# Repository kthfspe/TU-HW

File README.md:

# HW.template
Template for KiCAD PCB projects

## How to name your project
The kicad project name should be the name of the repo without the "-HW" part. For example EBS-HW repo should contain EBS.pro KiCAD project.  

The KiCAD project should be in the top level folder of the repo, i.e. no additional folders containing the KiCAD project should be there. To achieve that you will need to unselect an option when creating the project

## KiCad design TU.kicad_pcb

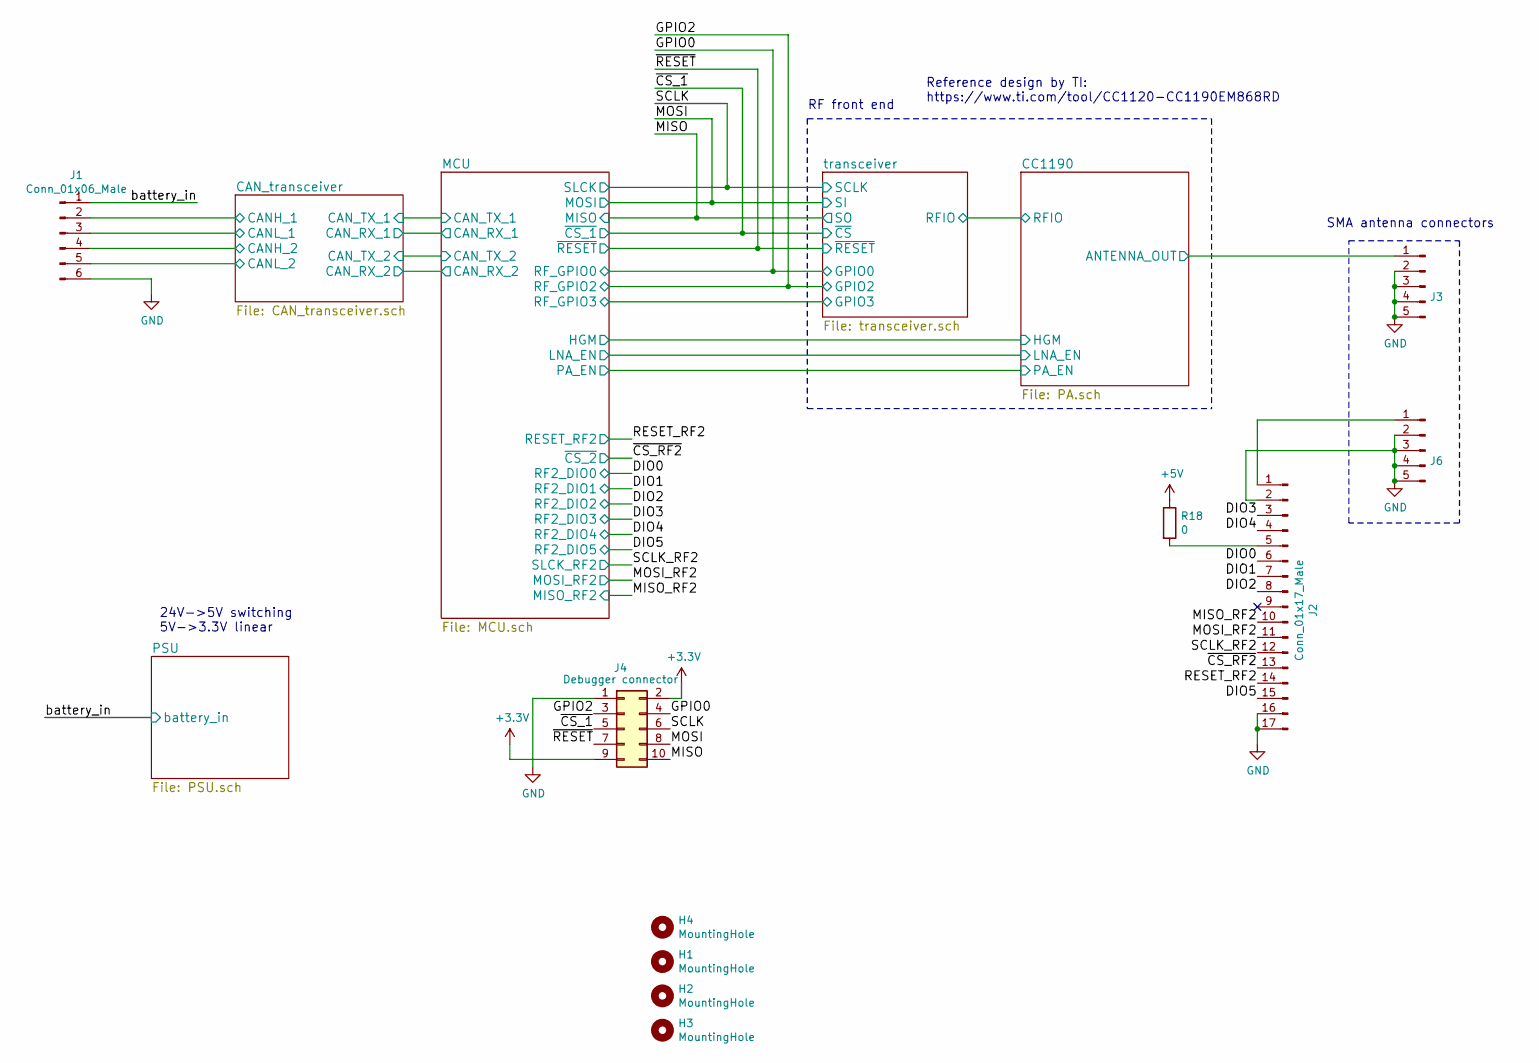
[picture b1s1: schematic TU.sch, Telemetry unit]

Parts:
H1, H2, H3, H4: MountingHole; MountingHole_2.5mm
J1: Conn_01x06_Male; TE_282834-6
J2: Conn_01x17_Male; RFM95PW
J3, J6: Conn_01x05_Male; Wurth_SMA_60312002114503
J4: Debugger connector; PinHeader_2x05_P2.54mm_Vertical
R18: 0; R_0603_1608Metric

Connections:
+3V3: J4.2, J4.9; also elsewhere on the board
+5V: R18.1; also elsewhere on the board
/CAN_transceiver/CANH_1: J1.2; also elsewhere on the board
/CAN_transceiver/CANH_2: J1.4; also elsewhere on the board
/CAN_transceiver/CANL_1: J1.3; also elsewhere on the board
/CAN_transceiver/CANL_2: J1.5; also elsewhere on the board
/CC1190/ANTENNA_OUT: J3.1; also elsewhere on the board
/DIO0: J2.6; also elsewhere on the board
/DIO1: J2.7; also elsewhere on the board
/DIO2: J2.8; also elsewhere on the board
/DIO3: J2.3; also elsewhere on the board
/DIO4: J2.4; also elsewhere on the board
/DIO5: J2.15; also elsewhere on the board
/GPIO0: J4.4; also elsewhere on the board
/GPIO2: J4.3; also elsewhere on the board
/MISO: J4.10; also elsewhere on the board
/MISO_RF2: J2.10; also elsewhere on the board
/MOSI: J4.8; also elsewhere on the board
/MOSI_RF2: J2.11; also elsewhere on the board
/RESET_RF2: J2.14; also elsewhere on the board
/SCLK: J4.6; also elsewhere on the board
/SCLK_RF2: J2.12; also elsewhere on the board
/battery_in: J1.1; also elsewhere on the board
/~CS_1: J4.5; also elsewhere on the board
/~CS_RF2: J2.13; also elsewhere on the board
/~RESET: J4.7; also elsewhere on the board
GND: J1.6, J2.2, J2.16, J2.17, J3.2, J3.3, J3.4, J3.5, J4.1, J6.2, J6.3, J6.4, J6.5; also elsewhere on the board
unnamed: J2.1, J6.1
unnamed: J2.5, R18.2

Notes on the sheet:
24V->5V switching 5V->3.3V linear
RF front end
SMA antenna connectors
Reference design by TI: https://www.ti.com/tool/CC1120-CC1190EM868RD

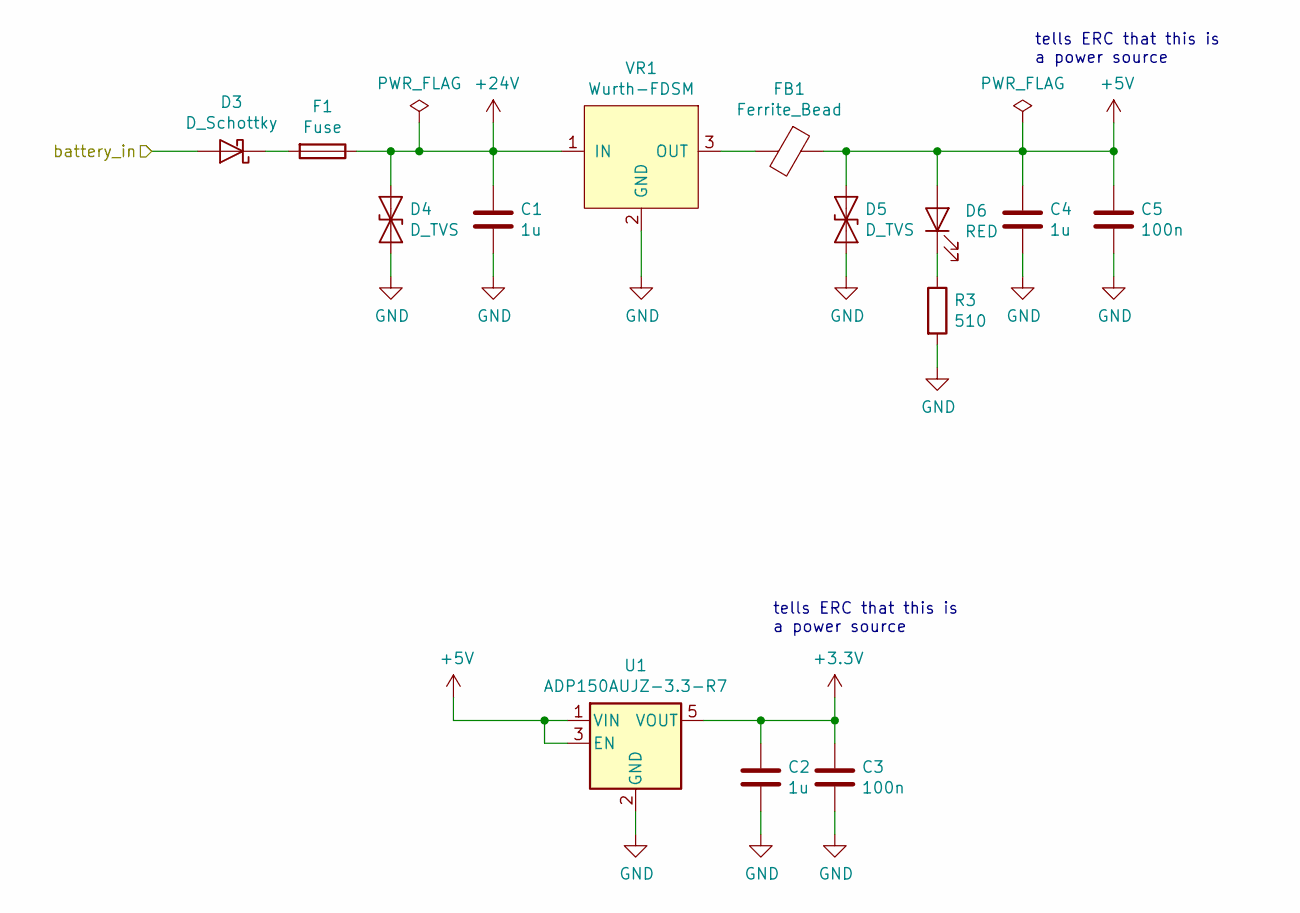
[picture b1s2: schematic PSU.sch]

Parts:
C1, C2: 1u; C_0805_2012Metric
C3, C5: 100n; C_0603_1608Metric
C4: 1u; C_0603_1608Metric
D3: D_Schottky; D_SOD-323
D4, D5: D_TVS; D_SOD-323
D6: RED; D_SOD-323
F1: Fuse; Fuse_0805_2012Metric
FB1: Ferrite_Bead; C_0805_2012Metric
R3: 510; R_0603_1608Metric
U1: ADP150AUJZ-3.3-R7; SOT-23-5
VR1: Wurth-FDSM

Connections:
+3V3: C2.1, C3.1, U1.5 (VOUT); also elsewhere on the board
+5V: C4.1, C5.1, D5.1 (A1), D6.2 (A), FB1.1, U1.1 (VIN), U1.3 (EN); also elsewhere on the board
+24V: C1.1, D4.1 (A1), F1.1, VR1.1 (IN)
/battery_in: D3.2 (A); also elsewhere on the board
GND: C1.2, C2.2, C3.2, C4.2, C5.2, D4.2 (A2), D5.2 (A2), R3.2, U1.2 (GND), VR1.2 (GND); also elsewhere on the board
unnamed: D3.1 (K), F1.2
unnamed: D6.1 (K), R3.1
unnamed: FB1.2, VR1.3 (OUT)

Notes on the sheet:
tells ERC that this is a power source

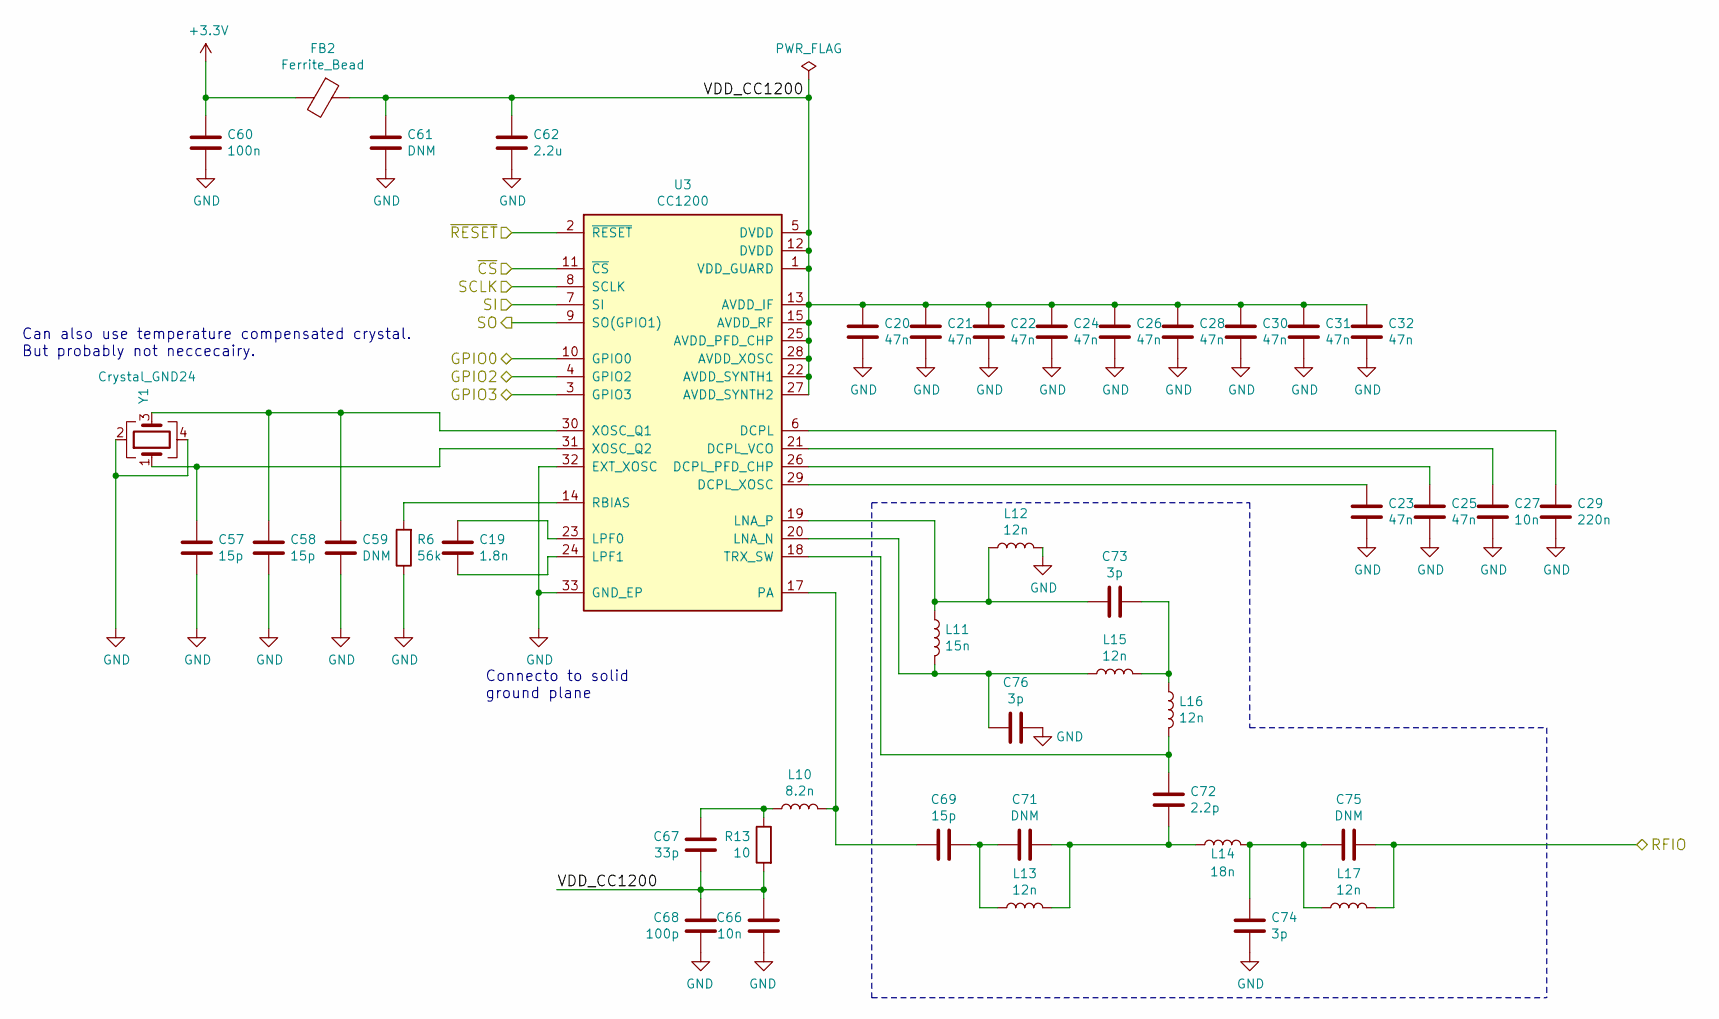
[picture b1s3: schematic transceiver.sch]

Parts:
C19: 1.8n; C_0603_1608Metric
C20, C21, C22, C23, C24, C25, C26, C28, C30, C31, C32: 47n; C_0603_1608Metric
C27, C66: 10n; C_0603_1608Metric
C29: 220n; C_0603_1608Metric
C57, C58, C69: 15p; C_0603_1608Metric
C59, C61, C71, C75: DNM; C_0603_1608Metric
C60: 100n; C_0603_1608Metric
C62: 2.2u; C_0603_1608Metric
C67: 33p; C_0603_1608Metric
C68: 100p; C_0603_1608Metric
C72: 2.2p; C_0603_1608Metric
C73, C74, C76: 3p; C_0603_1608Metric
FB2: Ferrite_Bead; C_0805_2012Metric
L10: 8.2n; L_0603_1608Metric
L11: 15n; L_0603_1608Metric
L12, L13, L15, L16, L17: 12n; L_0603_1608Metric
L14: 18n; L_0603_1608Metric
R6: 56k; R_0603_1608Metric
R13: 10; R_0603_1608Metric
U3: CC1200; QFN-32-1EP_5x5mm_P0.5mm_EP3.45x3.45mm
Y1: Crystal_GND24; ndk_08142018_NX3225SA

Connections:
+3V3: C60.1, FB2.2; also elsewhere on the board
/CC1190/RFIO: C75.1, L17.2; also elsewhere on the board
/GPIO0: U3.10 (GPIO0); also elsewhere on the board
/GPIO2: U3.4 (GPIO2); also elsewhere on the board
/MISO: U3.9 (SO(GPIO1)); also elsewhere on the board
/MOSI: U3.7 (SI); also elsewhere on the board
/SCLK: U3.8 (SCLK); also elsewhere on the board
/transceiver/GPIO3: U3.3 (GPIO3); also elsewhere on the board
/transceiver/VDD_CC1200: C20.1, C21.1, C22.1, C24.1, C26.1, C28.1, C30.1, C31.1, C32.1, C61.1, C62.1, C66.1, C67.2, C68.1, FB2.1, R13.2, U3.1 (VDD_GUARD), U3.5 (DVDD), U3.12 (DVDD), U3.13 (AVDD_IF), U3.15 (AVDD_RF), U3.22 (AVDD_SYNTH1), U3.25 (AVDD_PFD_CHP), U3.27 (AVDD_SYNTH2), U3.28 (AVDD_XOSC)
/~CS_1: U3.11 (~CS~); also elsewhere on the board
/~RESET: U3.2 (~RESET~); also elsewhere on the board
GND: C20.2, C21.2, C22.2, C23.2, C24.2, C25.2, C26.2, C27.2, C28.2, C29.2, C30.2, C31.2, C32.2, C57.2, C58.2, C59.2, C60.2, C61.2, C62.2, C66.2, C68.2, C74.2, C76.1, L12.2, R6.1, U3.32 (EXT_XOSC), U3.33 (GND_EP), Y1.2, Y1.4; also elsewhere on the board
unnamed: C19.1, U3.23 (LPF0)
unnamed: C19.2, U3.24 (LPF1)
unnamed: C23.1, U3.29 (DCPL_XOSC)
unnamed: C25.1, U3.26 (DCPL_PFD_CHP)
unnamed: C27.1, U3.21 (DCPL_VCO)
unnamed: C29.1, U3.6 (DCPL)
unnamed: C57.1, U3.31 (XOSC_Q2), Y1.1
unnamed: C58.1, C59.1, U3.30 (XOSC_Q1), Y1.3
unnamed: C67.1, L10.1, R13.1
unnamed: C69.1, C71.2, L13.1
unnamed: C69.2, L10.2, U3.17 (PA)
unnamed: C71.1, C72.2, L13.2, L14.1
unnamed: C72.1, L16.2, U3.18 (TRX_SW)
unnamed: C73.1, L15.2, L16.1
unnamed: C73.2, L11.1, L12.1, U3.19 (LNA_P)
unnamed: C74.1, C75.2, L14.2, L17.1
unnamed: C76.2, L11.2, L15.1, U3.20 (LNA_N)
unnamed: R6.2, U3.14 (RBIAS)

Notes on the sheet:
Connecto to solid ground plane
Can also use temperature compensated crystal. But probably not neccecairy.

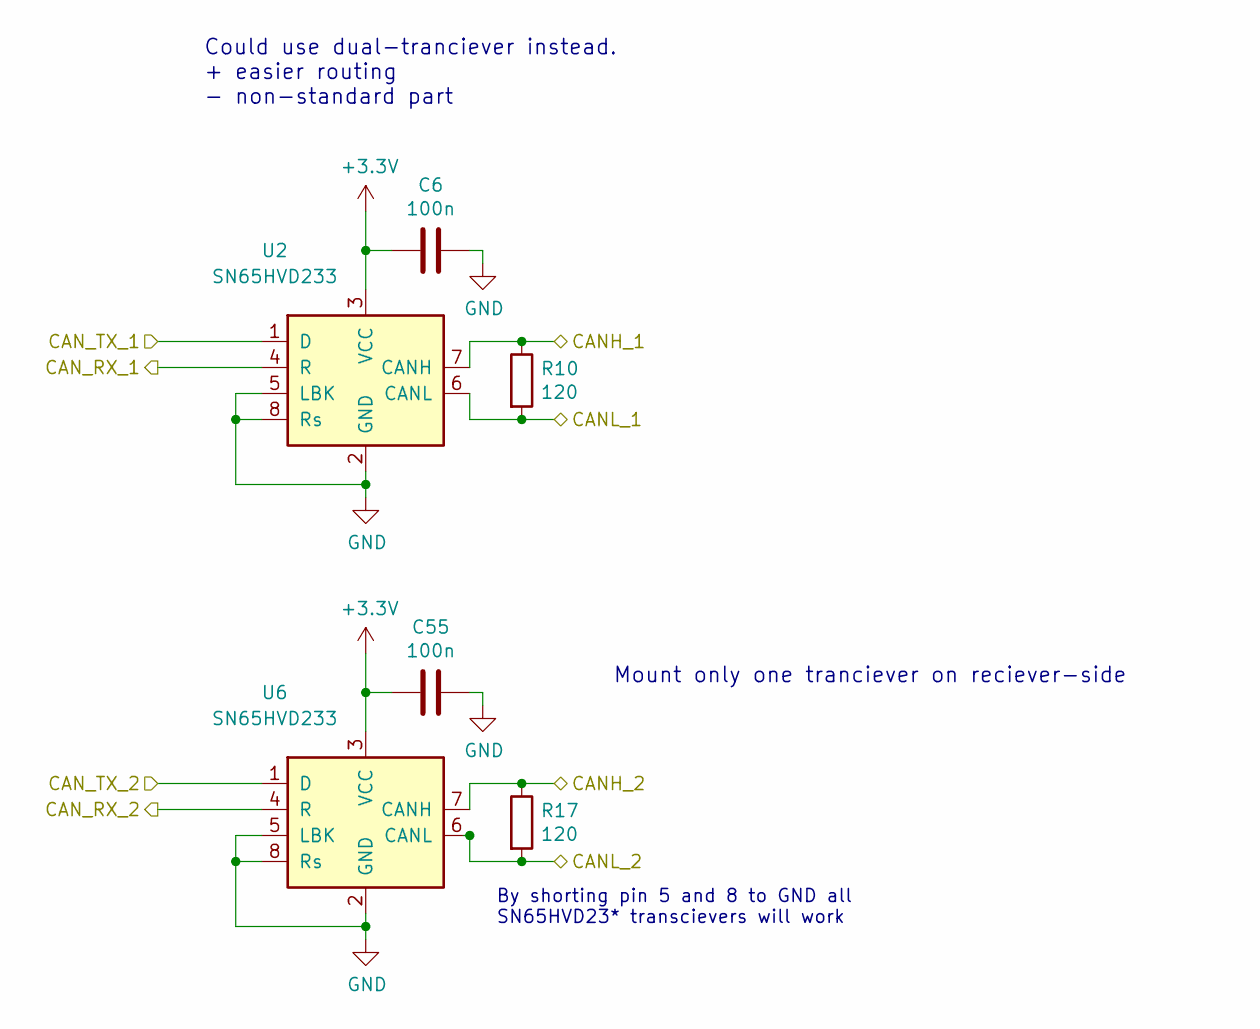
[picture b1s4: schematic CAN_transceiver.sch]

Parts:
C6, C55: 100n; C_0603_1608Metric
R10, R17: 120; R_0603_1608Metric
U2, U6: SN65HVD233; SOIC-8_3.9x4.9mm_P1.27mm

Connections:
+3V3: C6.2, C55.2, U2.3 (VCC), U6.3 (VCC); also elsewhere on the board
/CAN_transceiver/CANH_1: R10.1, U2.7 (CANH); also elsewhere on the board
/CAN_transceiver/CANH_2: R17.1, U6.7 (CANH); also elsewhere on the board
/CAN_transceiver/CANL_1: R10.2, U2.6 (CANL); also elsewhere on the board
/CAN_transceiver/CANL_2: R17.2, U6.6 (CANL); also elsewhere on the board
/CAN_transceiver/CAN_RX_1: U2.4 (R); also elsewhere on the board
/CAN_transceiver/CAN_RX_2: U6.4 (R); also elsewhere on the board
/CAN_transceiver/CAN_TX_1: U2.1 (D); also elsewhere on the board
/CAN_transceiver/CAN_TX_2: U6.1 (D); also elsewhere on the board
GND: C6.1, C55.1, U2.2 (GND), U2.5 (LBK), U2.8 (Rs), U6.2 (GND), U6.5 (LBK), U6.8 (Rs); also elsewhere on the board

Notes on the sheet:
By shorting pin 5 and 8 to GND all SN65HVD23* transcievers will work
Could use dual-tranciever instead. + easier routing - non-standard part
Mount only one tranciever on reciever-side

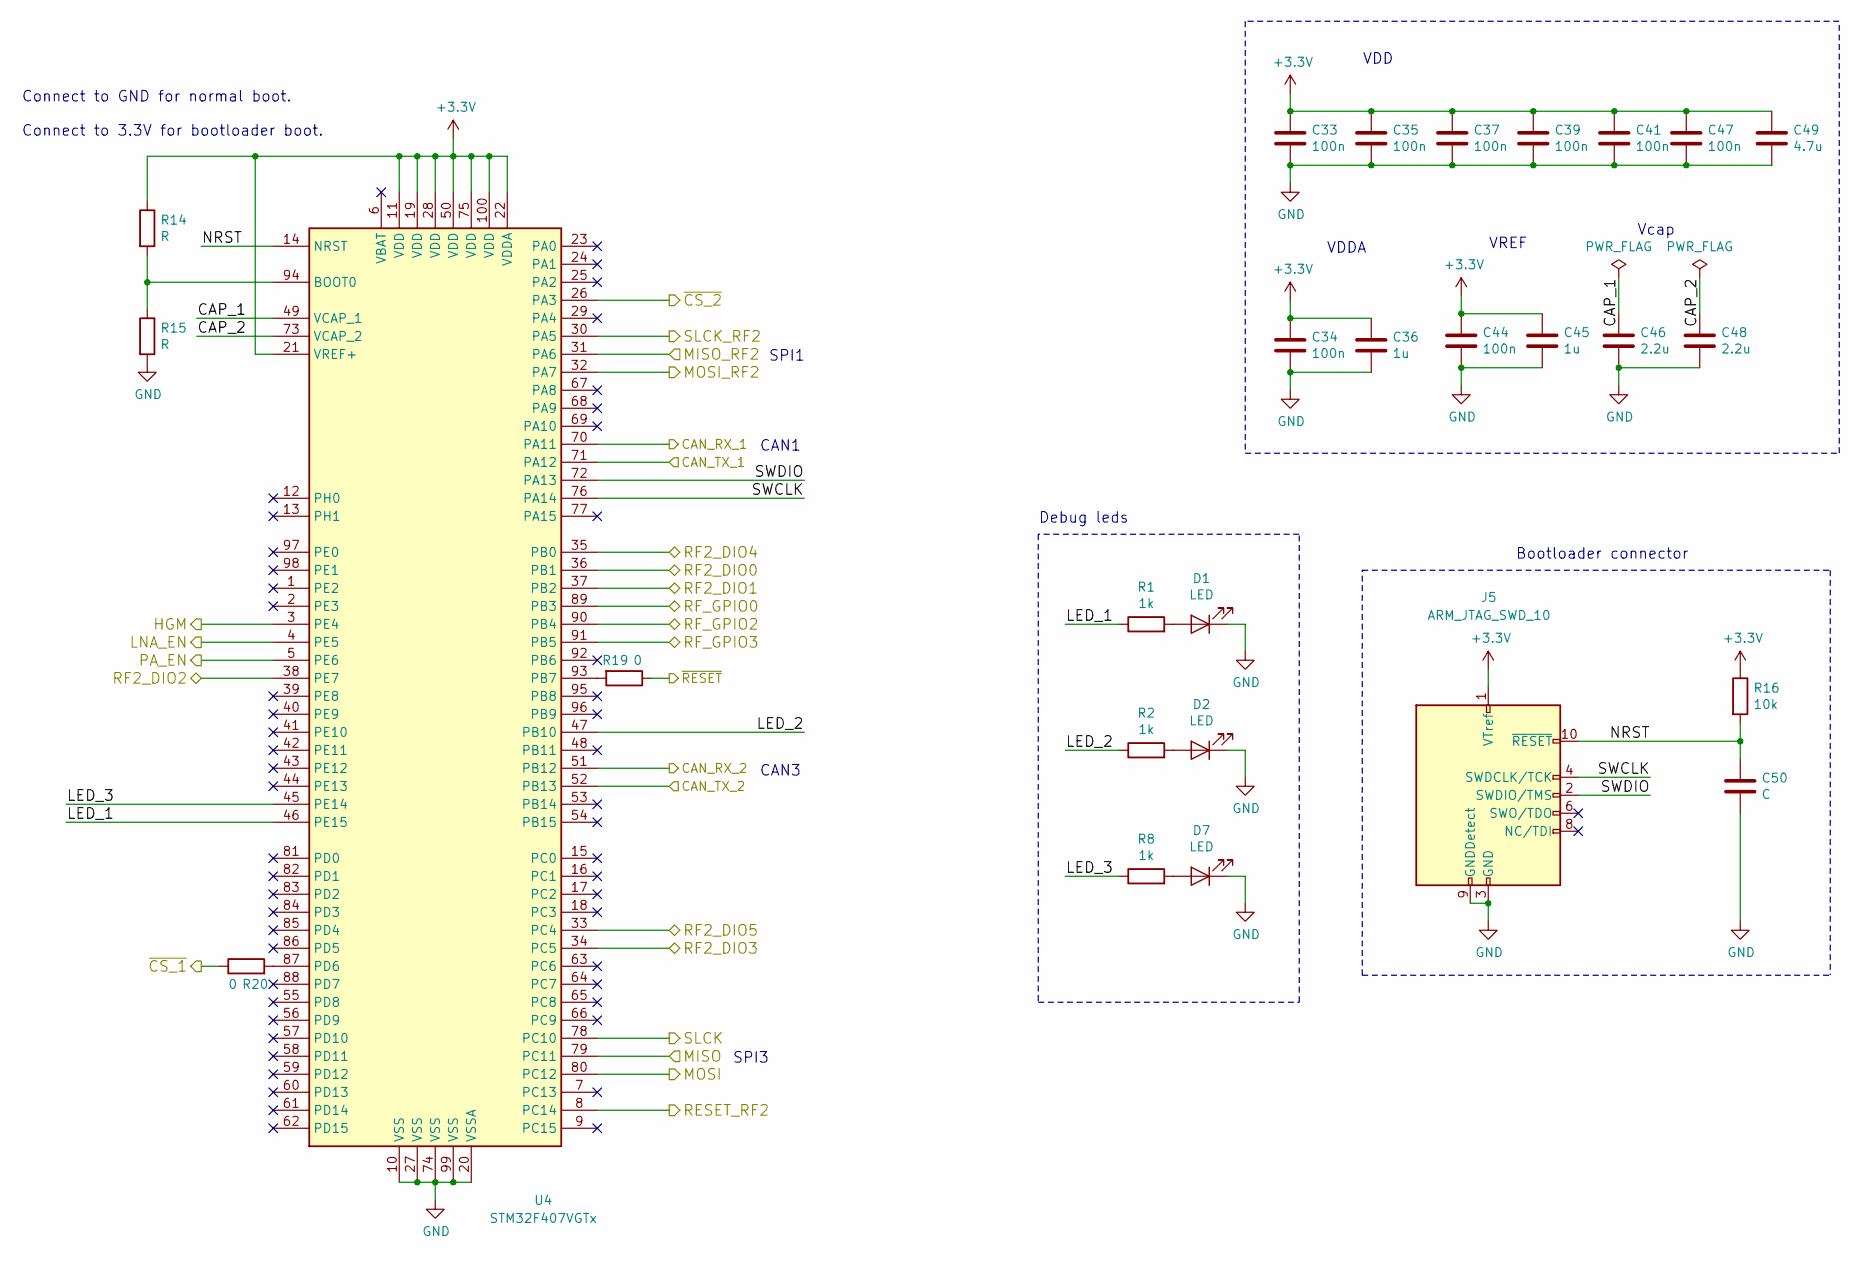
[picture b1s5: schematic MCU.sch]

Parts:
C33, C34, C35, C37, C39, C41, C44, C47: 100n; C_0603_1608Metric
C36, C45: 1u; C_0805_2012Metric
C46, C48: 2.2u; C_0603_1608Metric
C49: 4.7u; C_0603_1608Metric
C50: C; C_0603_1608Metric
D1, D2, D7: LED; D_0603_1608Metric
J5: ARM_JTAG_SWD_10; Atmel_ICP_connector
R1, R2, R8: 1k; R_0603_1608Metric
R14, R15: R; R_0603_1608Metric
R16: 10k; R_0603_1608Metric
R19, R20: 0; R_0603_1608Metric
U4: STM32F407VGTx; LQFP-100_14x14mm_P0.5mm

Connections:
+3V3: C33.1, C34.1, C35.1, C36.1, C37.1, C39.1, C41.1, C44.1, C45.1, C47.1, C49.1, J5.1 (VTref), R14.1, R16.1, U4.11 (VDD), U4.19 (VDD), U4.21 (VREF+), U4.22 (VDDA), U4.28 (VDD), U4.50 (VDD), U4.75 (VDD), U4.100 (VDD); also elsewhere on the board
/CAN_transceiver/CAN_RX_1: U4.70 (PA11); also elsewhere on the board
/CAN_transceiver/CAN_RX_2: U4.51 (PB12); also elsewhere on the board
/CAN_transceiver/CAN_TX_1: U4.71 (PA12); also elsewhere on the board
/CAN_transceiver/CAN_TX_2: U4.52 (PB13); also elsewhere on the board
/CC1190/HGM: U4.3 (PE4); also elsewhere on the board
/CC1190/LNA_EN: U4.4 (PE5); also elsewhere on the board
/CC1190/PA_EN: U4.5 (PE6); also elsewhere on the board
/DIO0: U4.36 (PB1); also elsewhere on the board
/DIO1: U4.37 (PB2); also elsewhere on the board
/DIO2: U4.38 (PE7); also elsewhere on the board
/DIO3: U4.34 (PC5); also elsewhere on the board
/DIO4: U4.35 (PB0); also elsewhere on the board
/DIO5: U4.33 (PC4); also elsewhere on the board
/GPIO0: U4.89 (PB3); also elsewhere on the board
/GPIO2: U4.90 (PB4); also elsewhere on the board
/MCU/CAP_1: C46.1, U4.49 (VCAP_1)
/MCU/CAP_2: C48.1, U4.73 (VCAP_2)
/MCU/LED_1: R1.1, U4.46 (PE15)
/MCU/LED_2: R2.1, U4.47 (PB10)
/MCU/LED_3: R8.1, U4.45 (PE14)
/MCU/NRST: C50.1, J5.10 (~RESET~), R16.2, U4.14 (NRST)
/MCU/SWCLK: J5.4 (SWDCLK/TCK), U4.76 (PA14)
/MCU/SWDIO: J5.2 (SWDIO/TMS), U4.72 (PA13)
/MISO: U4.79 (PC11); also elsewhere on the board
/MISO_RF2: U4.31 (PA6); also elsewhere on the board
/MOSI: U4.80 (PC12); also elsewhere on the board
/MOSI_RF2: U4.32 (PA7); also elsewhere on the board
/RESET_RF2: U4.8 (PC14); also elsewhere on the board
/SCLK: U4.78 (PC10); also elsewhere on the board
/SCLK_RF2: U4.30 (PA5); also elsewhere on the board
/transceiver/GPIO3: U4.91 (PB5); also elsewhere on the board
/~CS_1: R20.1; also elsewhere on the board
/~CS_RF2: U4.26 (PA3); also elsewhere on the board
/~RESET: R19.1; also elsewhere on the board
GND: C33.2, C34.2, C35.2, C36.2, C37.2, C39.2, C41.2, C44.2, C45.2, C46.2, C47.2, C48.2, C49.2, C50.2, D1.1 (K), D2.1 (K), D7.1 (K), J5.3 (GND), J5.5 (GND), J5.9 (GNDDetect), R15.2, U4.10 (VSS), U4.20 (VSSA), U4.27 (VSS), U4.74 (VSS), U4.99 (VSS); also elsewhere on the board
unnamed: D1.2 (A), R1.2
unnamed: D2.2 (A), R2.2
unnamed: D7.2 (A), R8.2
unnamed: R14.2, R15.1, U4.94 (BOOT0)
unnamed: R19.2, U4.93 (PB7)
unnamed: R20.2, U4.87 (PD6)

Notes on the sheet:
VDD
VDDA
Bootloader connector
Debug leds
CAN1
CAN3
SPI1
VREF
Vcap
Connect to GND for normal boot. Connect to 3.3V for bootloader boot.
SPI3

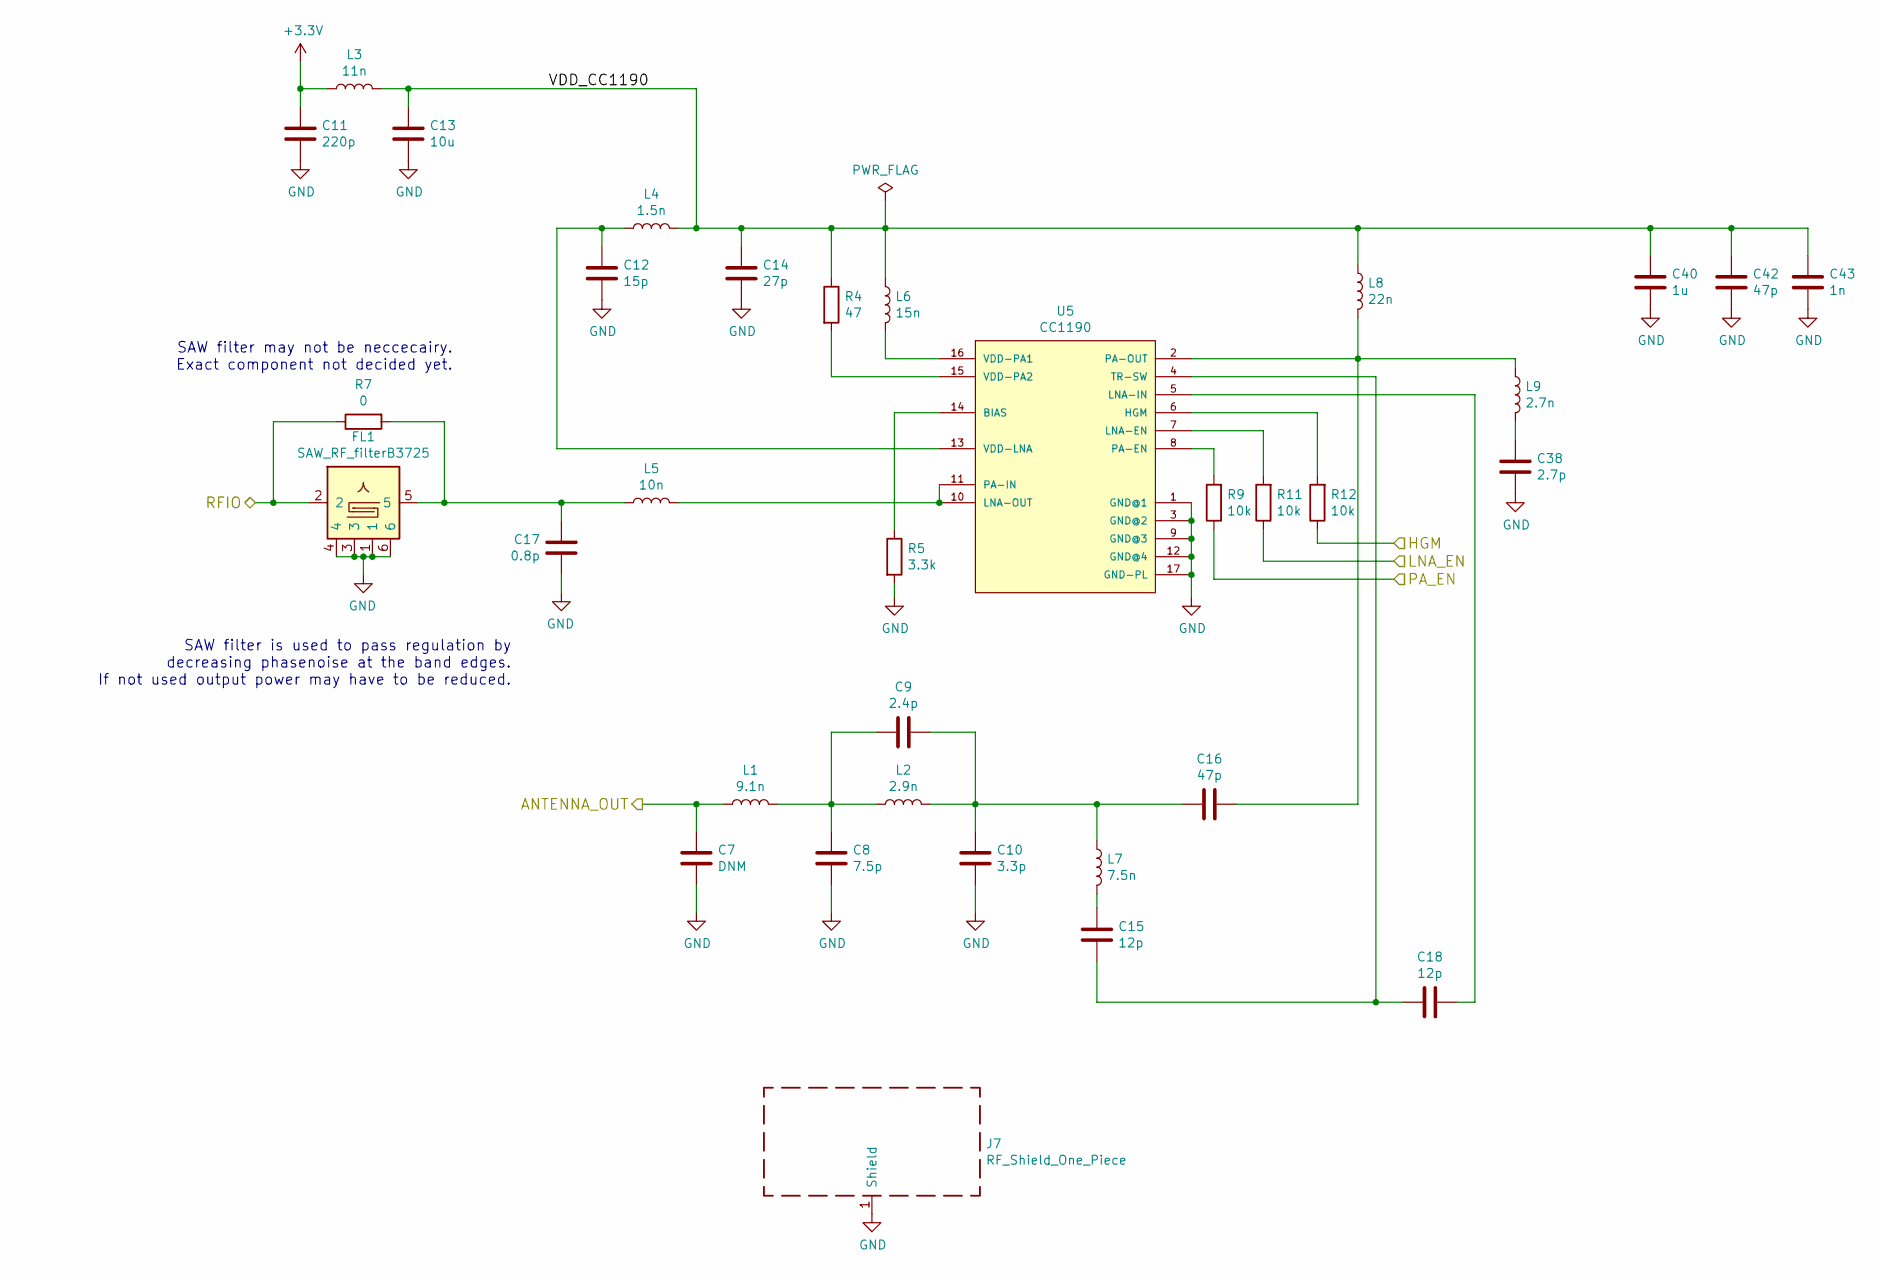
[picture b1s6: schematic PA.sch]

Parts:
C7: DNM; C_0603_1608Metric
C8: 7.5p; C_0603_1608Metric
C9: 2.4p; C_0603_1608Metric
C10: 3.3p; C_0603_1608Metric
C11: 220p; C_0603_1608Metric
C12: 15p; C_0603_1608Metric
C13: 10u; C_0603_1608Metric
C14: 27p; C_0603_1608Metric
C15, C18: 12p; C_0603_1608Metric
C16, C42: 47p; C_0603_1608Metric
C17: 0.8p; C_0603_1608Metric
C38: 2.7p; C_0603_1608Metric
C40: 1u; C_0603_1608Metric
C43: 1n; C_0603_1608Metric
FL1: SAW_RF_filterB3725; SON120P300X300X110-6N
J7: RF_Shield_One_Piece; WE_shield_20x20_36503205S
L1: 9.1n; L_0603_1608Metric
L2: 2.9n; L_0603_1608Metric
L3: 11n; L_0603_1608Metric
L4: 1.5n; L_0603_1608Metric
L5: 10n; L_0603_1608Metric
L6: 15n; L_0603_1608Metric
L7: 7.5n; L_0603_1608Metric
L8: 22n; L_0603_1608Metric
L9: 2.7n; L_0603_1608Metric
R4: 47; R_0603_1608Metric
R5: 3.3k; R_0603_1608Metric
R7: 0; R_0603_1608Metric
R9, R11, R12: 10k; R_0603_1608Metric
U5: CC1190; QFN-16-1EP_4x4mm_P0.65mm_EP2.15x2.15mm

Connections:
+3V3: C11.1, L3.1; also elsewhere on the board
/CC1190/ANTENNA_OUT: C7.1, L1.1; also elsewhere on the board
/CC1190/HGM: R9.1; also elsewhere on the board
/CC1190/LNA_EN: R11.1; also elsewhere on the board
/CC1190/PA_EN: R12.1; also elsewhere on the board
/CC1190/RFIO: FL1.2, R7.1; also elsewhere on the board
/CC1190/VDD_CC1190: C13.1, C14.1, C40.1, C42.1, C43.1, L3.2, L4.2, L6.1, L8.1, R4.1
GND: C7.2, C8.2, C10.2, C11.2, C12.2, C13.2, C14.2, C17.2, C38.2, C40.2, C42.2, C43.2, FL1.1, FL1.3, FL1.4, FL1.6, J7.1, R5.2, U5.1 (GND@1), U5.3 (GND@2), U5.9 (GND@3), U5.12 (GND@4), U5.17 (GND-PL); also elsewhere on the board
unnamed: C8.1, C9.2, L1.2, L2.1
unnamed: C9.1, C10.1, C16.2, L2.2, L7.1
unnamed: C12.1, L4.1, U5.13 (VDD-LNA)
unnamed: C15.1, L7.2
unnamed: C15.2, C18.2, U5.4 (TR-SW)
unnamed: C16.1, L8.2, L9.1, U5.2 (PA-OUT)
unnamed: C17.1, FL1.5, L5.1, R7.2
unnamed: C18.1, U5.5 (LNA-IN)
unnamed: C38.1, L9.2
unnamed: L5.2, U5.10 (LNA-OUT), U5.11 (PA-IN)
unnamed: L6.2, U5.16 (VDD-PA1)
unnamed: R4.2, U5.15 (VDD-PA2)
unnamed: R5.1, U5.14 (BIAS)
unnamed: R9.2, U5.8 (PA-EN)
unnamed: R11.2, U5.7 (LNA-EN)
unnamed: R12.2, U5.6 (HGM)

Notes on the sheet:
SAW filter may not be neccecairy. Exact component not decided yet.
SAW filter is used to pass regulation by decreasing phasenoise at the band edges. If not used output power may have to be reduced.

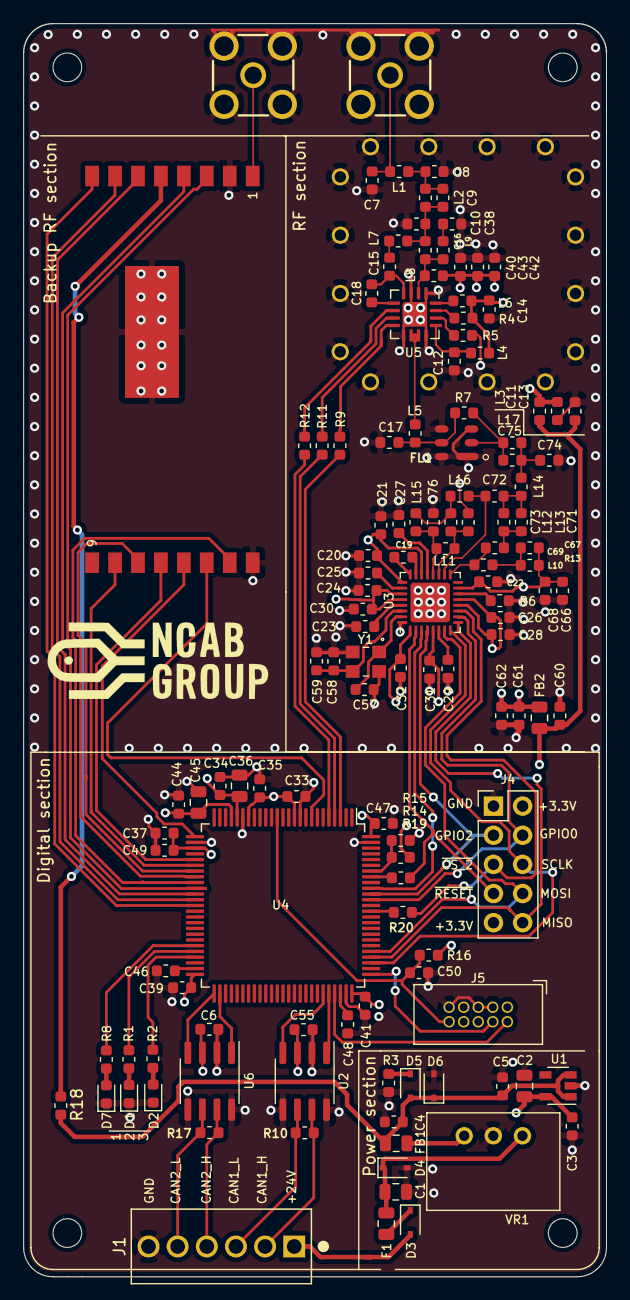
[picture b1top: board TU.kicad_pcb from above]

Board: 4 copper layers, 50.8 x 109.2 mm, 134 parts (0 on the bottom side), 92 nets.

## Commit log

2021-01-29 Created KiCad project
2021-01-29 Set up rough system block diagram
2021-01-29 Imported CAN and PSU blocks from infrastructure rep
2021-01-29 Fixed weird hierarchical sheets
2021-02-01 Added CC1190 library
2021-02-02 Added cc1190 reference design
    also changed cc1190 symbol
2021-02-02 Started work on CC1200
    might not be actual final tranciever
2021-02-04 Started work on MCU
2021-02-04 More work on tranciever and PA
2021-02-04 quick fix
2021-02-04 Added mount for RFM98/95
2021-02-04 Added component values for tranciever and PA
2021-02-10 Small changes to schematic
2021-02-10 Corrected some component values
2021-02-11 Added MCU config pins
2021-02-12 Changes to PA layout
2021-02-13 Changed to F4 MCU
2021-02-13 Even more small routing changes
2021-02-13 Revert "Even more small routing changes"
    This reverts commit 45de819c3fcd9a95750db64bc32d705dea6ff935.
2021-02-14 Lots of work on routing and pcb layout
2021-02-15 More routing changes
2021-02-16 Added edge cuts and silk screen comments
2021-02-16 Added mounting holes and terminal block
2021-02-16 Small tweaks
2021-02-16 Routed power for RF
2021-02-16 Feedback from peer review
2021-02-16 Added heatpad vias for extra rf module.
2021-02-16 Made sections clearer and cleaned up silkscreen.
2021-02-16 Added PA shield
2021-02-16 preliminairy routing of 50 ohm traces
2021-02-17 Added guard ring and cleaned up silkscreen
2021-02-17 Changed track width for 50 ohm traces
2021-02-17 Small changes to routing
2021-02-17 Fixed (most) pwr flag issues
2021-02-17 Added ncab logo
2021-04-10 Fixed HGM/PA mixup
